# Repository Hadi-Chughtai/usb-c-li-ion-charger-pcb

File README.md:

# TP4056 USB-C Lithium-Ion Charger PCB

This is a KiCad project for a small printed circuit board that charges a single lithium-ion cell from USB-C.

It started as a battery charger I built in LTspice. That circuit was only a simulation — every part in it was fake, just math that acted like a charger. This project turns that simulation into a real board design with real parts that can be bought and soldered.

> This board is a finished design, but it has not been ordered, assembled, or tested yet. The design files are fabrication-ready.

The goal was simple, and I set it at the start:

- take the LTspice circuit and turn it into a board that could actually be made,
- keep it simple and easy to follow,
- list the real parts needed and how each one connects,
- and do the full PCB layout, not just the schematic.

This was my first PCB. I picked this project on purpose: I wanted to learn the whole process (simulation, schematic, footprints, layout, checking, factory files) on a circuit I already understood, instead of copying a tutorial board that means nothing to me.

Where it ended up: a finished two-layer board, 36 mm × 13.5 mm, that charges one Li-ion cell at 1 A from USB-C, with a red light for "charging" and a green light for "done." The schematic check came back clean, the layout check came back with zero errors and nothing left unconnected, and the factory files are made and checked.

## Where It Started: The LTspice Simulation

The LTspice circuit was not made of real parts. Each block just acted out one job of a charger:

- **A 5 V source** — pretending to be a USB power supply.
- **A fake regulator** — a math block that pushed exactly 1 A into the battery at first, then less and less as the battery filled up. You cannot buy this. It only exists inside the simulation.
- **A fake battery** that acted like a 3,000 mAh cell getting fuller.
- **A charge counter** built around a huge 10,800 F capacitor. 10,800 is not a random number: a 3,000 mAh battery holds 10,800 coulombs of charge, so this capacitor "counted" how much charge had gone into the battery.
- **A "done" switch** that stopped the charge once the battery was over 4.1 V and the current had dropped under 100 mA, and stayed off.

The full simulation is in my [CC/CV charger simulation](https://github.com/Hadi-Chughtai/CC-CV-Simulation) project.

So the spec the real board had to match was:

```text
Charge at 1.0 A at first (constant current).
At 4.2 V, hold the voltage and let the current drop on its own (constant voltage).
Stop at 100 mA — one tenth of the starting current — and show "done."
Battery: one 3.7 V Li-ion/LiPo cell, 3,000 mAh.
```

## The Main Idea

Most of the LTspice circuit should not be on the board at all. The regulator, the fake battery, the charge counter, and the done switch were only there to make the simulation behave. Real hardware does not need them, because one cheap chip already does all of that by itself: the TP4056.

It charges at a set current (up to 1 A), holds 4.2 V at the end, stops on its own when the current drops to a tenth, and has two pins that can light an LED to say "charging" or "done." That is exactly what my simulation did, which is why I picked it.

So the real work was translation. Go through the simulation one block at a time and ask: in real life, what part does this job? And if the answer is "nothing — that was only there for the simulation," delete it.

## How Each Part of the Simulation Became a Real Part

- **5 V ideal source → J1, a USB-C socket (power-only type).** A real board needs a real plug for power. USB-C because every cable on my desk is USB-C.
- **Nothing in the simulation → R4 and R5, two 5.1 kΩ resistors on the socket's CC1 and CC2 pins.** A USB-C power supply gives out nothing until it sees these two resistors. They are how the board "asks" for power. The simulation never needed them because its 5 V source was always on.
- **The fake regulator (1 A, then taper at 4.2 V) → U1, the TP4056 charger chip.** This one chip does the whole charging job the fake block was acting out.
- **The charge current, which was just a number inside the fake block → R1, a 1.2 kΩ resistor on the chip's PROG pin.** On the real chip, one resistor sets the charge current. 1.2 kΩ = 1 A, the same current my simulation used.
- **The fake battery → J2, a 2-pin JST-PH socket (pin 1 = BAT+, pin 2 = GND).** The fake battery becomes a real battery that stays off the board and plugs in. JST-PH is the plug that real LiPo pouch batteries come with.
- **The charge counter (10,800 F capacitor) → nothing. Deleted.** It only existed so the simulation could count charge. The real chip knows when to stop by itself, so no part is needed.
- **The "done" switch → the chip's STDBY pin (pin 6), through R3 (1 kΩ), to D2, a green LED.** When the chip finishes charging, this pin turns the green "done" LED on. Same job as the fake switch, done by the chip.
- **Nothing in the simulation → the chip's CHRG pin (pin 7), through R2 (1 kΩ), to D1, a red LED.** Added for the real board: a red "charging" light, so the board tells you what it is doing instead of you watching a graph.
- **Nothing — fake parts do not need it → C1 and C2, two 10 µF capacitors,** one on the +5V input and one on the battery side. Real chips need a capacitor close by to stay stable. The simulation hid this completely.
- **Setup pins → the chip's TEMP pin (pin 1) wired to GND, and its CE pin (pin 8) wired to +5V.** Grounding TEMP turns off temperature sensing (I did not use a temperature sensor), and CE to +5V means "always on when plugged in."
- **Ground → a sheet of copper covering both sides of the board,** not single wires. Explained further down.

## Charge Current

The charge current is set by R1 on the PROG pin. For the TP4056, the relationship is:

```text
Charge current (mA) = 1200 / R1 (kΩ)
```

In this design:

```text
R1 = 1.2 kΩ
1200 / 1.2 = 1000 mA
```

So the board charges at:

```text
1 A
```

The status pins work by connecting to ground when they are on, so each LED sits between +5V and its pin, with a 1 kΩ resistor (R2, R3) to limit the current. With about 2 V across the LED:

```text
LED current ≈ (5 V - 2 V) / 1000 Ω = 3 mA
```

## Decisions I Made, and Why

1. **Use my own simulation instead of a tutorial board.** I had looked at tutorial boards first and dropped them — they felt random and I would not use them for anything. Bigger boards (a buck converter, a motor driver, a microcontroller board) were honestly too hard for a first PCB. This way the circuit was already in my head and the only new thing to learn was PCB design itself.
2. **One chip (TP4056) does all the charging.** It matches my simulation's numbers exactly, it only needs a few parts around it, and it is a common, proven chip.
3. **USB-C for power in, the power-only version of the socket.** USB-C is what I actually have cables for. The power-only socket has no data pins, which kept the schematic simple. The cost of that choice is the two CC resistors — worth it, and I learned something real from them.
4. **1.2 kΩ for R1.** That sets 1 A, the same as my simulation, and 1 A suits a 3,000 mAh cell and most medium-size pouch batteries.
5. **An LED on each status pin, each with a 1 kΩ resistor.** Red = charging, green = done.
6. **0805 size for all the small parts.** It is the biggest common surface-mount size, so if I solder this by hand later, it is the easiest size to work with.
7. **TEMP pin to ground, CE pin on.** The simplest setup that is still correct: no temperature sensor, charger runs whenever it is plugged in.
8. **All parts on the front of the board.** The USB-C socket only mounts on top, and the LEDs need to face up so you can see them. Keeping every part on one side also makes soldering simpler. The back of the board is still used — for the ground copper and for one track that needed to cross.
9. **Route the tracks by hand, not with an autorouter.** The board only has 7 nets, doing it myself kept the two power tracks wide, and routing it myself was the skill I was trying to learn.
10. **No warnings at all, not just no errors.** When the board check reported warnings about the printed labels, I decided I wanted the report completely empty, not just "good enough." How that was done is in the checking section below.
11. **Stop at the design — do not order it yet.** I priced it up: the boards themselves are only about $2–4, but fast shipping was $25, slower shipping about $9, and a US maker (OSH Park) would be $3.76 for three boards. There is no deadline forcing my hand, so I kept the finished, checked design and left ordering as something I can do any time with one upload.

## Step 1: The Schematic

I placed the 12 real parts in KiCad's schematic editor — the chip (U1), the two sockets (J1, J2), five resistors, two capacitors, and two LEDs — and wired them up following the translation list above. Checking the schematic properly caught mistakes that looking at it had not:

- **Parts sitting next to each other are not the same as parts connected.** In my first attempt, several wires only looked joined. I went back through the connection list one wire at a time until every join was real.
- **PROG, CC1, and CC2 were wrong at first.** I had wired them straight to ground. They have to go through their resistors — the resistor is the whole point of those pins. Fixed by routing each one through R1, R4, and R5.
- **Both LEDs were in backwards.** The chip's status pins connect to ground when they turn on, so the LED has to face +5V, not the chip. I flipped both LEDs and checked again.
- **Things were missing.** The battery socket, the USB socket's ground and shield connections, and the part values all had to be added before the schematic was actually complete.
- **The schematic check (ERC) reported two errors at the end:** "power pin not driven" on +5V and GND. That error is normal for this board — the power comes in through a passive USB socket, so there is no power source on the board for the checker to see. The fix is two PWR_FLAG symbols, which just tell the checker "this net is powered from outside, on purpose."

Result of this step: ERC fully clean, and every value set:

```text
R1 = 1.2 kΩ
R2 = 1 kΩ
R3 = 1 kΩ
R4 = 5.1 kΩ
R5 = 5.1 kΩ
C1 = 10 µF
C2 = 10 µF
```

## Step 2: Footprints

A footprint is the pattern of metal pads a part solders onto, so each schematic part needed the right one. All the small parts got 0805 footprints so the board stays easy to solder by hand. The two sockets got footprints made for those exact parts:

```text
U1       HSOP-8 with a ground pad underneath (3.9 × 4.9 mm)
J1       Made for the exact GCT USB4135-GF-A socket, top-mount, 6-pin
J2       JST PH vertical, 2.00 mm pitch
R1–R5    0805
C1–C2    0805
D1–D2    0805, with the polarity marked
```

One mistake here: the LEDs briefly had the capacitor footprint. I caught it in the assignment list and changed both to the LED footprint, which matters because LEDs have a right way round and the LED footprint marks it.

One thing to remember from this step: the USB socket footprint fits one exact part (GCT USB4135-GF-A), so that is the part to buy if the board gets built.

## Step 3: Placing the Parts and the Board Outline

KiCad turns the schematic into a pile of footprints joined by thin lines (the ratsnest) showing what has to connect to what. I placed the parts so the power flows left to right, the same way the circuit reads: USB socket on the left edge, the chip in the middle, its input capacitor (C1) just left of it and battery capacitor (C2) just right of it, and the battery socket on the right edge. R4 and R5 sit right above the USB socket's CC pins, and R1 and the LED parts sit above the chip, near the pins they connect to.

My first placement put the battery socket on the far left, which would have dragged the BAT+ track across the whole board, and a couple of parts were hanging off the board edge — I scrapped that layout and redid it the way described above.

The outline is a rectangle drawn on the Edge.Cuts layer. Its bottom edge sits exactly on the USB socket's own "PCB Edge" line, so the socket ends up flush with the edge of the board, like a port on a real product. The other three sides have about 3 mm of spare room. Final size:

```text
36 mm × 13.5 mm, 1.6 mm thick
```

Roughly the footprint of a AA battery, but flat.

## Ground Is a Sheet of Copper, Not Wires

Instead of drawing ground wires, I drew a copper zone over the whole board and told it "you are GND." Every ground pad touches that copper, so ground connects itself.

My first try only filled the bottom layer, which does not work on its own — the parts sit on top, so their ground pads are on the top layer. Once the zone was set to both layers and refilled, almost every ground line in the ratsnest disappeared in one go.

## Routing the Tracks by Hand

Seven nets were left to route. I did them on the top layer, in this order, on purpose:

```text
Widths: 0.5 mm for the two tracks that carry the full 1 A (+5V in, and BAT+)
        0.25 mm for everything else
Order:  BAT+ first, then +5V, then the two short CC tracks,
        then PROG, then the two LED chains last
```

BAT+ came out as one straight line from the chip, through C2, to the battery socket. The +5V track joins the USB socket's two power pins, then C1, then the chip.

The one crossing problem: the green LED's track (STDBY) had to get from above the chip to pin 6 on the chip's other side, and every top-layer path crossed something else. Instead of going the long way around the edge of the board, I dropped it through a via (a small plated hole) to the back layer, ran it under the chip, and came back up through a second via into pin 6. The back track passes under the chip's ground pad in the top view, which is fine — the board itself is the insulation between the layers. This was the first time I used vias to route, not just to connect ground.

Moving parts to the back is a common trick to untangle a layout. I looked at it and did not use it, for the reasons in decision 8.

## Step 4: Checking the Board (DRC)

The first full check (DRC) reported 21 problems plus 2 unconnected pads. That sounds bad, but reading them one by one, they were really three real problems and a pile of cosmetic ones:

- **U1 pins 1 and 3 (both GND) not connected properly — 3 errors.** Those two ground pins were boxed in by the STDBY via and the PROG track, so the ground copper could not reach them properly. Fix: vias placed in the pins themselves, tying pins 1 and 3 and the chip's big centre ground pad straight into the bottom copper, which was well connected.
- **Board outline is malformed (crosses itself) — 1 error.** My outline edit had left overlapping outline shapes. Cleaned it back to one rectangle and re-ran the check — gone.
- **Printed labels (silkscreen) sitting on pads or on other parts' outlines — 19 warnings.** Cosmetic only — the factory just does not print the parts of a label that fall on a pad. Since I wanted a completely empty report, I removed them all at once: one bulk edit moved every part label off the printing layer onto the Fab layer. The labels are still there in KiCad when I need them for soldering; they just will not be printed.
- **Two drill holes in exactly the same place (at U1 pin 3) — 1 warning, showed up on the re-check.** The pin-3 fix had left two identical vias stacked in one spot. Deleted one and checked the pin was still connected.

Final check:

```text
0 errors, 0 warnings, 0 unconnected pads
```

Everything in the layout is connected the way the schematic says.

There was one more check after that, at the factory's website. Their preview of the back of the board looked wrong to me at first — nearly all plain green, with one diagonal line. I went through it item by item and it was right: the back is ground copper covered by the green coating, so it looks blank; the two pads you can see are the battery socket's pins from behind, which is why they are on the opposite side; and the diagonal line is my STDBY track on the back — it slopes the other way because you are looking at the board from the other side, like a reflection. Their system also read the board size back as 13.5 × 36 mm and 2 layers, which matched my outline exactly.

## Step 5: The Files a Factory Needs

A factory does not take the KiCad file. It takes Gerber files — one file per layer (top copper, bottom copper, the green coating layers, the printing layers, the paste layers, and the board outline) — plus drill files that say where every hole goes.

I exported all of them and then opened the zip and checked it file by file before uploading: 12 files, and in particular both drill files were in there. Without the drill files the board would come back with no holes in it.

I also put my name on the board: printed text on the back, in the big empty area, with a title and version line under it ("TP4056 USB-C Li-Ion Charger · Rev 1 · 2026"). Text on the back looks backwards in the editor, because you are looking through the board — on the real board, flipped over, it reads normally.

## How You Would Actually Use It

The board does not hold a battery and nothing slots into it. It sits between a power supply and a battery, like an adapter.

A USB-C cable plugs into the left end, the same as plugging a cable into a phone. The battery is a flat silver pouch with a red wire and a black wire already attached, ending in a small white plug — that plug pushes into the white socket on the right end of the board, and the battery just lies next to the board on the desk. Inside the plug, the red wire lands on pin 1 (BAT+) and the black wire on pin 2 (GND). The plug only fits one way round, but it is still worth one look before the first use, because a few batteries are wired the other way round and that would damage the chip.

Red light on means it is charging. Green light on means the battery is full and the charger has stopped by itself — unplug it and use the battery. The chip gets warm while charging at 1 A, which is normal for this chip.

## Final Specs

```text
What it does:   Charges one Li-ion/LiPo cell. Charging only — nothing else.
Power in:       USB-C, 5 V. Best from a wall adapter, not a laptop port.
How it charges: 1.0 A until the cell reaches 4.2 V, then holds 4.2 V
                while the current drops, and stops at 100 mA.
Lights:         Red LED on = charging. Green LED on = finished.
Battery:        JST-PH 2-pin plug (pin 1 = BAT+, pin 2 = GND).
                The battery is not on the board — it plugs in and sits next to it.
Board:          2 layers, 36 × 13.5 × 1.6 mm, ground copper on both sides.
Parts:          12, all surface-mount, all on the front.
Checks:         Schematic check clean.
                Layout check: 0 errors, 0 warnings, 0 unconnected.
```

## Parts List

```text
U1       1×  TP4056 chip — does all the charging
J1       1×  USB-C socket, GCT USB4135-GF-A (power-only) — where the 5 V comes in
J2       1×  JST-PH 2-pin socket — where the battery plugs in
R1       1×  1.2 kΩ, 0805 — sets the charge current to 1 A
R2, R3   2×  1 kΩ, 0805 — one for each LED, to limit its current
R4, R5   2×  5.1 kΩ, 0805 — the USB-C CC resistors
C1, C2   2×  10 µF, 0805 — one on the input, one on the battery side
D1       1×  Red LED, 0805 — "charging" light
D2       1×  Green LED, 0805 — "done" light
```

## Files in This Repo

```text
kicad/        schematic and PCB layout (made in KiCad 10)
fabrication/  Gerber and drill files, plus a zip ready to upload to a fab house
images/       the LTspice simulation, schematic, layout, and 3D views of the board
```

## Limitations

This project is a board design. It shows the charger design and that the design passes KiCad's checks, but the board itself has not been built yet.

It does not include:

- an assembled or tested board,
- battery temperature sensing (the TEMP pin is grounded),
- a protection circuit or a power output — it only charges, and the battery comes off the charger to be used somewhere else,
- charging for more than one cell, or for anything other than a single 3.7 V Li-ion/LiPo cell,
- or USB data / fast-charge negotiation — the input is always 5 V.

The charge current is also fixed by R1. Changing the 1 A charge rate means changing that resistor value in the design.

If I do order it later, everything is ready: order the boards, buy the 12 parts on the list above — including the exact GCT USB socket the footprint needs — solder them on, and test it with a real battery: red light when it is plugged in, green light at 4.2 V. At that point this page gets one new line: built and tested.

Next board I have planned: an LM358 op-amp amplifier (the gain is set by a knob — a 100 kΩ potentiometer — from 1× to 11×, running on 9 V). Same process, an analogue circuit this time.

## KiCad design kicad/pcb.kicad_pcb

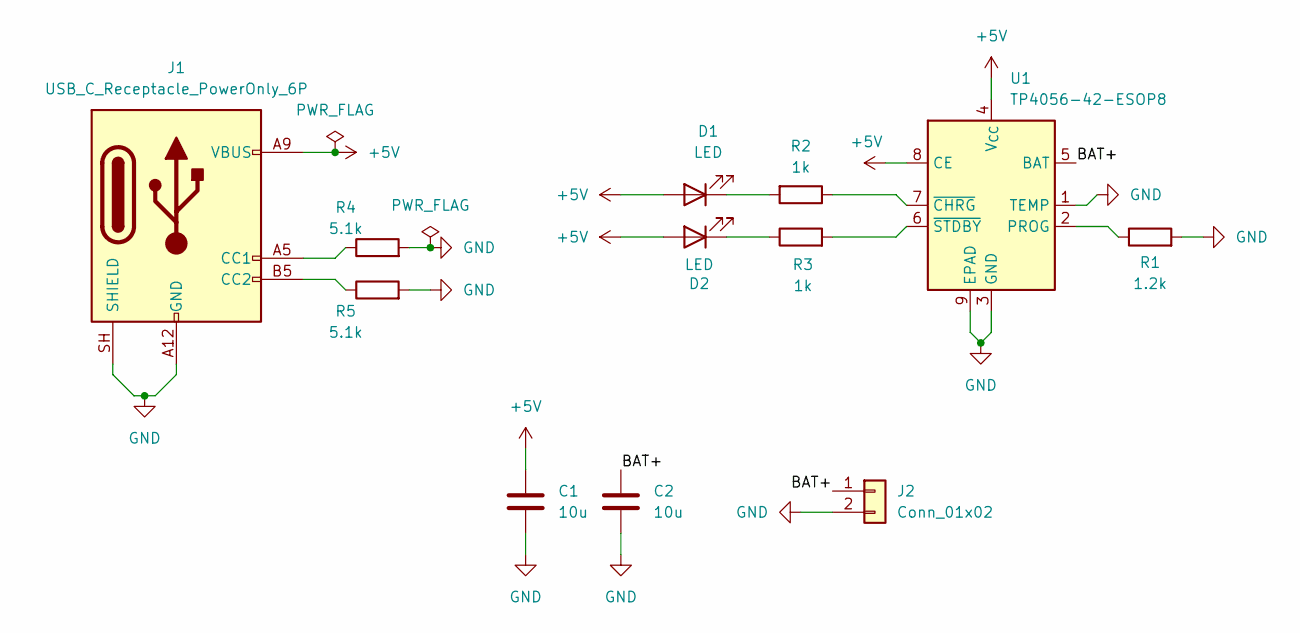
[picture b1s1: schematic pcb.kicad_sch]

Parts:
C1, C2: 10u; C_0805_2012Metric
D1, D2: LED; LED_0805_2012Metric
J1: USB_C_Receptacle_PowerOnly_6P; USB_C_Receptacle_GCT_USB4135-GF-A_6P_TopMnt_Horizontal
J2: Conn_01x02; JST_PH_B2B-PH-K_1x02_P2.00mm_Vertical
R1: 1.2k; R_0805_2012Metric
R2, R3: 1k; R_0805_2012Metric
R4, R5: 5.1k; R_0805_2012Metric
U1: TP4056-42-ESOP8; HSOP-8-1EP_3.9x4.9mm_P1.27mm_EP2.41x3.1mm

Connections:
+5V: C1.1, D1.2 (A), D2.2 (A), J1.A9 (VBUS), J1.B9 (VBUS), U1.4 (V_{CC}), U1.8 (CE)
/BAT+: C2.1, J2.1, U1.5 (BAT)
GND: C1.2, C2.2, J1.A12 (GND), J1.B12 (GND), J1.SH (SHIELD), J2.2, R1.2, R4.2, R5.2, U1.1 (TEMP), U1.3 (GND), U1.9 (EPAD)
unnamed: D1.1 (K), R2.2
unnamed: D2.1 (K), R3.1
unnamed: J1.A5 (CC1), R4.1
unnamed: J1.B5 (CC2), R5.1
unnamed: R1.1, U1.2 (PROG)
unnamed: R2.1, U1.7 (~CHRG)
unnamed: R3.2, U1.6 (~STDBY)

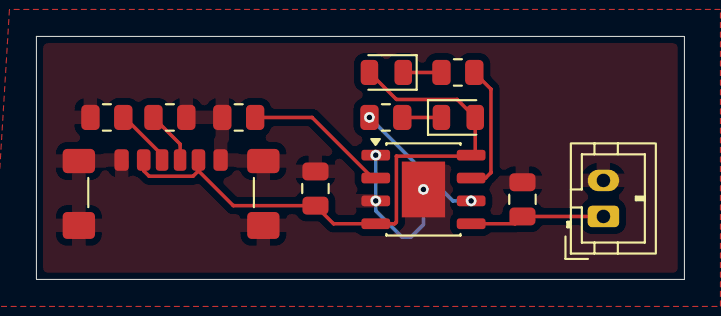
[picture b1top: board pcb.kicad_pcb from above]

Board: 2 copper layers, 36.0 x 13.5 mm, 12 parts (0 on the bottom side), 10 nets.
